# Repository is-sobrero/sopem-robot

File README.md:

<h1 align="center">SoPEM Robot</h1>
<div align="center">
      <br>
      <i>Clicca la copertina per guardare il video di presentazione</i><br><br><br>
      
</div>

# Tabella dei contenuti
- [Introduzione](#introduzione)
- [Filosofia Open Source in ogni aspetto](#filosofia-open-source-in-ogni-aspetto)
- [Singoli componenti](#singoli-componenti)
- [Licenza](#licenza)
  - [Autori / Copyright](#autori--copyright)
  - [Dettagli licenza](#dettagli-licenza)

# Introduzione
SoPEM è un robot di tipologia rover studiato appositamente per le finali delle Olimpiadi di Robotica 2020 (anche se in lockdown).
Sfruttando materiali di riciclo, sono stati costruiti 3 robot, dall'aspetto diverso ma tutti e tre volti allo stesso scopo: monitorare i valori di PM10 delle città in modo autonomo con un sensore autocostruito con materiali di riciclo (Un LED infrarosso ricavato da un telecomando e un fotodiodo da un vecchio decoder).

In complemento al robot, è stata sviluppata una applicazione che permette di impostare il percorso da far eseguire al robot e per ottenere i valori di PM10 in tempo reale. 
L'applicazione, sviluppata tramite il framework Flutter, è compatibile con la maggior parte delle piattaforme software attuali: Android, iOS, Web, macOS, Windows e Linux.

Non avendo a disposizione uno strumento di calibrazione professionale, per ottenere valori affidabili è stato creato un modello di machine learning che, addestrato con i dati del sensore e delle stazioni di rilevamento dell’ARPA, è in grado di fornire dati affidabili per il 71%.

# Filosofia Open Source in ogni aspetto
Il robot, oltre ad essere completamente Open Source, è anche sviluppato con strumenti Open Source: da Micropython a Flutter, da KiCad ad Arduino, tutti questi strumenti sono completamente Open e supportati dalla community FOSS e OSHW.

# Singoli componenti
- [Motor Controller](https://github.com/is-sobrero/sopem-robot/tree/master/Software/Motor%20Controller)
- [Robot](https://github.com/is-sobrero/sopem-robot/tree/master/Software/Robot)
- [SoPEM Companion](https://github.com/is-sobrero/sopem-robot/tree/master/Software/sopem_companion)
- [SoPEM Fitter](https://github.com/is-sobrero/sopem-robot/tree/master/Machine%20Learning)
- [Sensore PM10](https://github.com/is-sobrero/sopem-robot/tree/master/Hardware/dust_sensor)

# Licenza
## Autori / Copyright
Copyright 2020 (c) I.S. "A. Sobrero" / SoRobot Team
## Dettagli licenza
Il codice sorgente è rilasciato in licenza secondo GNU General Public License v3.0, che garantisce le quattro regole fondamentali del software libero anche sui fork del firmware del robot.
Le schematiche dell'Hardware sono rilasciate in licenza secondo CERN Open Hardware Licence v1.2, che definisce le condizioni entro cui le schematiche possono essere usate, modificate e distribuite.
Per maggiori dettagli riguardo la licenza, consultare il file [LICENSE](https://github.com/is-sobrero/sopem-robot/blob/master/LICENSE) generale per la repo oppure i file LICENSE per le singole componenti.

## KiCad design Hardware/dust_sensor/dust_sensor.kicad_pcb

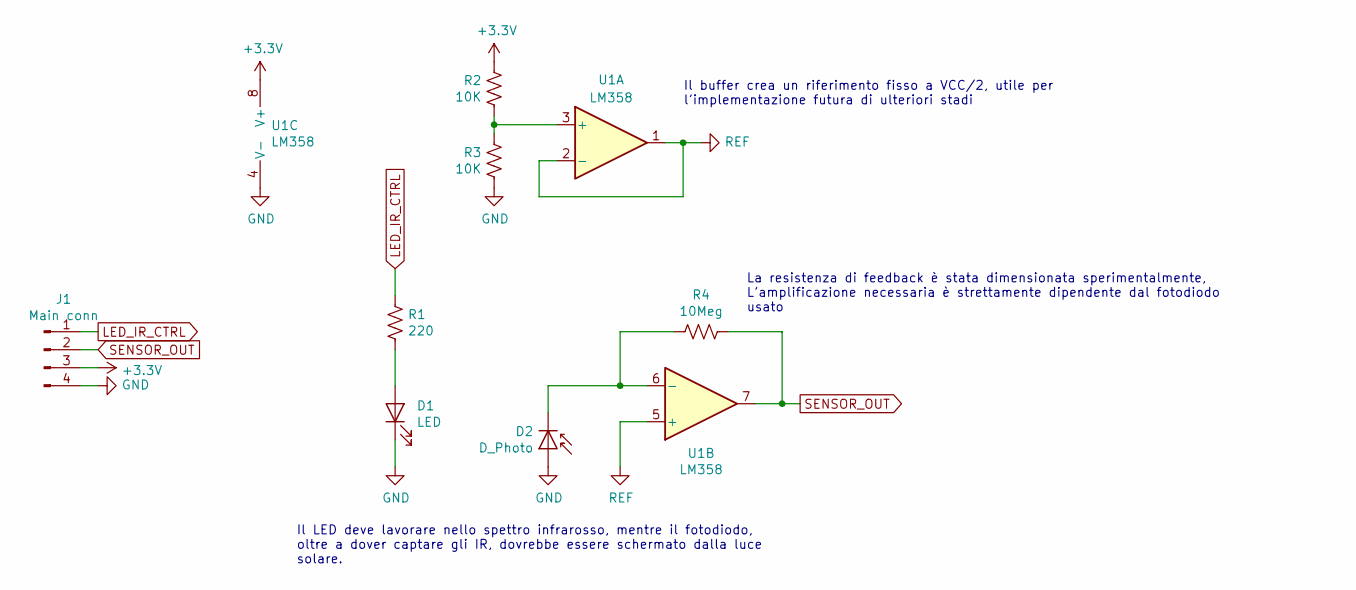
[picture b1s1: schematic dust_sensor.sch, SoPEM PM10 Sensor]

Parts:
D1: LED; LED_D5.0mm_Horizontal_O1.27mm_Z3.0mm_Clear
D2: D_Photo; LED_D5.0mm_Horizontal_O1.27mm_Z3.0mm_IRBlack
J1: Main conn; PinHeader_1x04_P2.54mm_Vertical
R1: 220; R_Axial_DIN0207_L6.3mm_D2.5mm_P7.62mm_Horizontal
R2, R3: 10K; R_Axial_DIN0207_L6.3mm_D2.5mm_P7.62mm_Horizontal
R4: 10Meg; R_Axial_DIN0207_L6.3mm_D2.5mm_P7.62mm_Horizontal
U1: LM358; DIP-8_W7.62mm_LongPads

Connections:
+3V3: J1.3, R2.2, U1.8 (V+)
GND: D1.1 (K), D2.2 (A), J1.4, R3.1, U1.4 (V-)
LED_IR_CTRL: J1.1, R1.2
unnamed: D1.2 (A), R1.1
unnamed: D2.1 (K), R4.2, U1.6 (-)
unnamed: R2.1, R3.2, U1.3 (+)
REF: U1.1, U1.2 (-), U1.5 (+)
SENSOR_OUT: J1.2, R4.1, U1.7

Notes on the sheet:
Il buffer crea un riferimento fisso a VCC/2, utile per l’implementazione futura di ulteriori stadi
La resistenza di feedback è stata dimensionata sperimentalmente, L’amplificazione necessaria è strettamente dipendente dal fotodiodo usato
Il LED deve lavorare nello spettro infrarosso, mentre il fotodiodo, oltre a dover captare gli IR, dovrebbe essere schermato dalla luce solare.

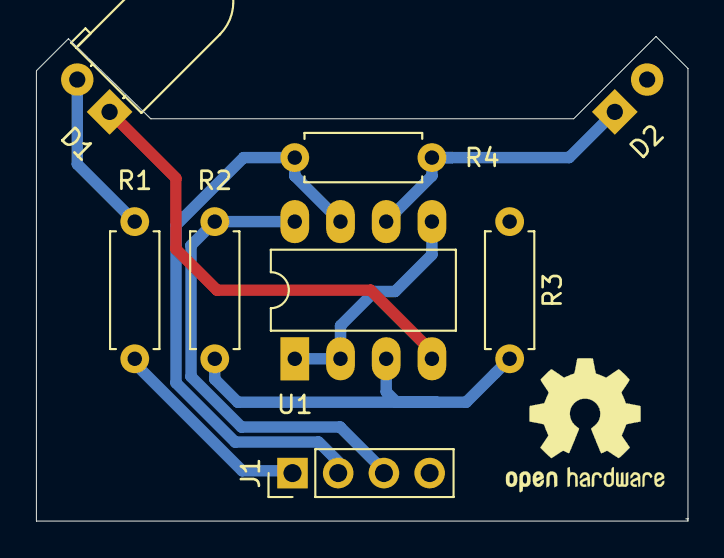
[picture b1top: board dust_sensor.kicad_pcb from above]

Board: 2 copper layers, 36.2 x 26.9 mm, 8 parts (1 on the bottom side), 8 nets.

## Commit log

2020-06-24 Uploaded dust sensor documentation
2020-06-27 Uploaded SoPEM Companion sources
2020-06-27 Code cleanup
2020-06-27 Updated license for Companion
2020-06-27 Minor UI Changes
2020-06-28 Uploaded ML sources
2020-06-28 Uploaded motor controller sources
2020-06-28 Update README.md
    repair element that can be dangerous for mind health of a Mathematician,
    we also remind 10 in maths.
2020-06-29 Uploaded robot source code
